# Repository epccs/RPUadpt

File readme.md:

# RPUadpt (/w 328pb)

From <https://github.com/epccs/RPUadpt/>

## Overview

Shield used to connect a controller board to a multi-drop serial bus (e.g. [RPUbus]). Modular 8P8C connectors allow RJ-45 connectors and CAT5 to run the differential pairs between locations. The robust noise immunity of the differential pairs allows a host computer (e.g. Pi Zero with [RPUpi], or desktop with [USBuart]) to interface with and bootload the controller board(s) in noisy environments over serial hardware that can be physically secured.

[RPUbus]: https://rpubus.org/
[USBuart]: https://github.com/epccs/Driver/tree/master/USBuart
[RPUpi]: https://github.com/epccs/RPUpi

An SPI interface with a level shifting buffer is available between the controller and computer. SPI is also wired to an optional header for a slave device (e.g. an [SD card]) that the controller can access. 

[SD card]: https://www.adafruit.com/product/254

I2C between the manager and the controller allows its program to read an address and make the serial connection active. I2C between manager and host allows the host computer to set a bootload address even when its local controller lacks I2C interfacing software. 

[RPUno]: https://github.com/epccs/RPUno
[Irrigate7]: https://github.com/epccs/Irrigate7
[Punica]: https://github.com/epccs/Punica

[Forum](https://rpubus.org/bb/viewforum.php?f=7)

[HackADay](https://hackaday.io/project/17719-rpuadpt)

## Status

[Available](https://rpubus.org/Order_Form.html)

This shield is programmed with an in-circuit serial programming tool that is able to handle the 3.3V ATmega328p target. I use an Arduino Uno with the [ArduinoISP] sketch and an SPI level shifter (e.g. [ICSP]). A Raspberry Pi should also work with the avrdude bit-bang (-c linuxgpio) or SPI (-c linuxspi) modes.

[ICSP]: https://github.com/epccs/Driver/tree/master/ICSP

[ArduinoISP]: https://github.com/arduino/Arduino/blob/master/build/shared/examples/11.ArduinoISP/ArduinoISP/ArduinoISP.ino

## [Hardware](./Hardware)

Hardware files and notes for referance.

## Example

This multi-drop serial bus allows multiple controller boards to be connected to a host serial port (UART). Crossover of the serial from the host computer occurs as it enters the transceivers on the shield. The differential pair from the transceives is run through patch cables (CAT5) between the controllers, so all the controllers see the same interface. 

The transceivers differential driver is enabled when a UART pulls its TX output low, which means no software [magic] is needed to operate the push to talk of the transceivers, though it is up to the user software to ensure the controllers talk in a reasonable way (e.g. without collision). Since the drivers in the transceivers only output an inverted level they can't cross conduct thus collisions don't damage the hardware. I see collisions when accidentally connecting two shields with the same address and both try to answer.

[magic]: https://github.com/pyserial/pyserial/blob/master/serial/rs485.py

In the above drawing, the computer can communicate with the three controller boards (an [RPUno], an [Irrigate7], and a [Punica]). The computer connected with USB to the RPUftdi shield can access the controller boards when the manager allows. The Raspberry Pi can also access the controller boards when the manager allows. Only one host computer should access the serial bus at a time. The RS-422 can be run a significate distance (perhaps over 1000 meters). 

In my firmware examples (e.g. see [RPUno]) a command processor is used to accept textual commands over the wired interface. The examples have a simple makefile that compiles the microcontroller firmware from the source. The host computers I use have the AVR toolchain from Debian installed and can compile and upload that firmware over the serial interface with the uploader tool (avrdude). 

The firmware examples use a makefile with a bootload rule (e.g. "make bootload") that uploads to the targets bootloader. Building without a rule (e.g. "make") compiles the firmware into a relocatable elf as expected but turns that into an Intel formate hex file, the bootload rule just sends that to the uploader tool. 

When the serial port on the host opens (e.g. PySerial, picocom, or the toolchain uploader tool) it pulls the nDTR and nRTS line low (they are active low) and that tells the manager firmware ([Remote] on RPUadpt and [Host2Remote] on [RPUftdi]) to send the bootload address on the DTR pair (i.e. start its bootloader with a reset), and lockout other host. PySerial needs to wait for a few seconds while the bootloader timeout finishes (an Arduino Uno also needs to wait for this timeout).

[Remote]: https://github.com/epccs/RPUadpt/tree/master/Remote
[Host2Remote]: https://github.com/epccs/RPUftdi/tree/master/Host2Remote

The manager can see (nDTR and nRTS) the host try to connect and if it is not blocked by another host will broadcast a bootload address. When the managers see the address on the DTR pair (note the local manager will also see it) then everything sets lockout_active except if the localhost_active is set then the host remains connected and also the addressed manager remains connected and sets bootloader_started. Again the address is in the manager on the shield, so the address follows the shield. Replacing the controller (e.g. swapping an [RPUno] with an [Irrigate7]) does not change the address, but replacing the shield does (the address on the shield may be programmed).

^6 has an ATmega328pb with a second I2C port, one for the control board and the other for the host. The details of how the host will use it are not yet known. Only the single board computers with Linux (e.g. Raspberry Pi) can do things with I2C at a reasonable price. For the host, I will probably expose the commands to read the local address and set the bootload address. If the host reads the local address then sneaky mode should probably end with a normal mode broadcast on the DTR pair (but that is TBD). 

^6 also has some SPI options that need to be tested, but until an evaluation is done using it is at your own risk.

## AVR toolchain

The core files for this board are in the /lib folder. Each example has its files and a Makefile in its own folder. The toolchain packages that I use are available on Debain, Ubuntu and Raspbian. 

```
sudo apt-get install git gcc-avr binutils-avr gdb-avr avr-libc avrdude
git clone https://github.com/epccs/RPUadpt
```

* [gcc-avr](https://packages.ubuntu.com/search?keywords=gcc-avr)
* [binutils-avr](https://packages.ubuntu.com/search?keywords=binutils-avr)
* [gdb-avr](https://packages.ubuntu.com/search?keywords=gdb-avr)
* [avr-libc](https://packages.ubuntu.com/search?keywords=avr-libc)
* [avrdude](https://packages.ubuntu.com/search?keywords=avrdude)

The ATmega328pb is not in mainline, so the files from Atmel [atpack] (DFP.1.2.209.atpack) are included in this repo for use with avr-gcc (GCC) 5.4.0. At the time of this writing Raspbian has avr-gcc (GCC) 4.9.2 which does not support atpack files.

[atpack]: http://packs.download.atmel.com/

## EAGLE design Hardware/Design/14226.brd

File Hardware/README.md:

# Hardware

## Overview

This shield board plugs into a control board (e.g. [RPUno], [Irrigate7], or [Punica]) to interface it with a multi-drop serial bus. 

[RPUno]: https://github.com/epccs/RPUno
[Irrigate7]: https://github.com/epccs/Irrigate7
[Punica]: https://github.com/epccs/Punica

## Inputs/Outputs/Functions

```
        Full Duplex serial RX and TX lines
        Half Duplex management line DTR
        RX, TX, and management lines connect to RS-485 tranceivers
        Differential pairs from transceivers allow multi-drop of the serial connections
        The transceivers receiver has Fail Safe so all see 0V as a HIGH.
        Power is taken from +5V of the control board.
        TWI0 (I2C) interface between local programable unit and manager.
        TWI1 (I2C) interface between local host and manager.
        IOFF buffers are used for UART and SPI host interface.
        IOFF allows the serial and control to remain functional when the host is powered down.
        UART and SPI interface buffers work with host voltage 5V to 1.8V.
```

## Uses

```
        Daisy chain serial from multiple control boards to a host.
        Use a point to point mode to bootload firmware to an addressed target.
        Use SPI to transfer data from a local host master to local programable unit slave.
        Or use the SPI local programable unit as master to operate a MicroSD card as slave.
```

## Notice

The serial port is a wired connection. The hardware is raw and lacks training wheels (i.e. it is not a polished product). The ATmega328pb toolchain is not widely available (e.g. {Debain: {stretch:no, buster:yes, sid:yes}} )

# Table Of Contents

1. [Status](#status)
2. [Design](#design)
3. [Bill of Materials](#bill-of-materials)
4. [How To Use](#how-to-use) 

# Status

```
        ^6  Done: Design, Layout, BOM, Review*, Order Boards, Assembly, Testing, Evaluation.
            WIP: 
            Todo:  
            *during review the Design may change without changing the revision.
            add IOFF buffer between host (e.g. offboard FTDI Friend) and tranceiver like RPUpi has
            add IOFF buffer between optional host SPI and controler like RPUpi
            add chip sellect from the host to IO10 (which has nSS, it is missing on RPUpi)
            SPI pinout can match MicroSD card breakout (https://www.adafruit.com/product/254)
            add a jumper to power the SPI from the controller (e.g. RPUno +5V)
            remove ADC6 connction to voltage divider of +5V pin.

        ^5 Done: Design, Layout, BOM, Review*, Order Boards, Assembly, Testing, Evaluation.
           removed from tindie is used in some locations.
```

Debugging and fixing problems i.e. [Schooling](./Schooling/)

Setup and methods used for [Evaluation](./Evaluation/)

# Design

The board is 0.063 thick, FR4, two layer, 1 oz copper with ENIG (gold) finish.

## Electrical Parameters (Typical)

```
        5V pin needs 150mA (RPUno has over 1A) to power RPU_BUS
        This is OSH so refer to the parts used for storage and operation limits.
```

## Electrical Schematic

## Testing

Check correct assembly and function with [Testing](./Testing/)

# Bill of Materials

The BOM is a CVS file, import it into a spreadsheet program like LibreOffice Calc (or Excel), or use a text editor.

Option | BOM's included
----- | ----- 
A. | [BRD] 
M. | [BRD] [SMD] [HDR] 
Y. | [BRD] [SMD] [HDR] [CAT5]

[BRD]: ./Design/14226BRD,BOM.csv
[SMD]: ./Design/14226SMD,BOM.csv
[HDR]: ./Design/14226HDR,BOM.csv
[CAT5]: ./Design/14226CAT,BOM.csv

# How To Use

## ICSP

[ArduinoISP] sketch is on an [Uno] and a level converter (e.g. [ICSP]) is between the boards. I then run the build rule (e.g. "make isp") to program the bus manager with the [Remote] firmware. With that, I can plug the RPUadpt into an RPUno and serial bootload the controller firmware (e.g. [Solenoid] with [K3]). An RPUftdi and Uno clone can be used with a host to communicate with the RPUadpt and its controller board. Additional boards will need the [Remote] firmware to have the bus address set in EEPROM.

[ArduinoISP]: https://github.com/arduino/Arduino/blob/master/build/shared/examples/11.ArduinoISP/ArduinoISP/ArduinoISP.ino
[Uno]: https://www.adafruit.com/product/50
[ICSP]: https://github.com/epccs/Driver/tree/master/ICSP
[Remote]: ../Remote
[Solenoid]: https://github.com/epccs/RPUno/tree/master/Solenoid
[K3]: https://github.com/epccs/Driver/tree/master/K3

__WARNING: The shield will be damaged if removed from a powered MCU board. Before separating the shield from the MCU board it is very important to check that all power sources are disconnected.__

The CAT5 needs wired just like an Ethernet cable following [T568A] (or T568B) method. 

[T568A]: https://en.wikipedia.org/wiki/Category_5_cable

Grounding should occur at one location only. If a RPUftdi is used then the host frame will be connected to the local earth grounding system through USB. Unfortunately, the ground wires within CAT5 will not survive a lightning strike and will bring it to the host. To reduce the risk run a #14 AWG ground wire between the remote device and the ground system connected to the host chassis. Also, the host chassis needs a good (#14 AWG or larger) wire to the same ground system (see NEC sec 250). 

The RX, TX, and DTR pair need a 100 Ohm termination on each end of the CAT5 daisy chain. I'm going to supply a RJ45 plug with terminations for now.

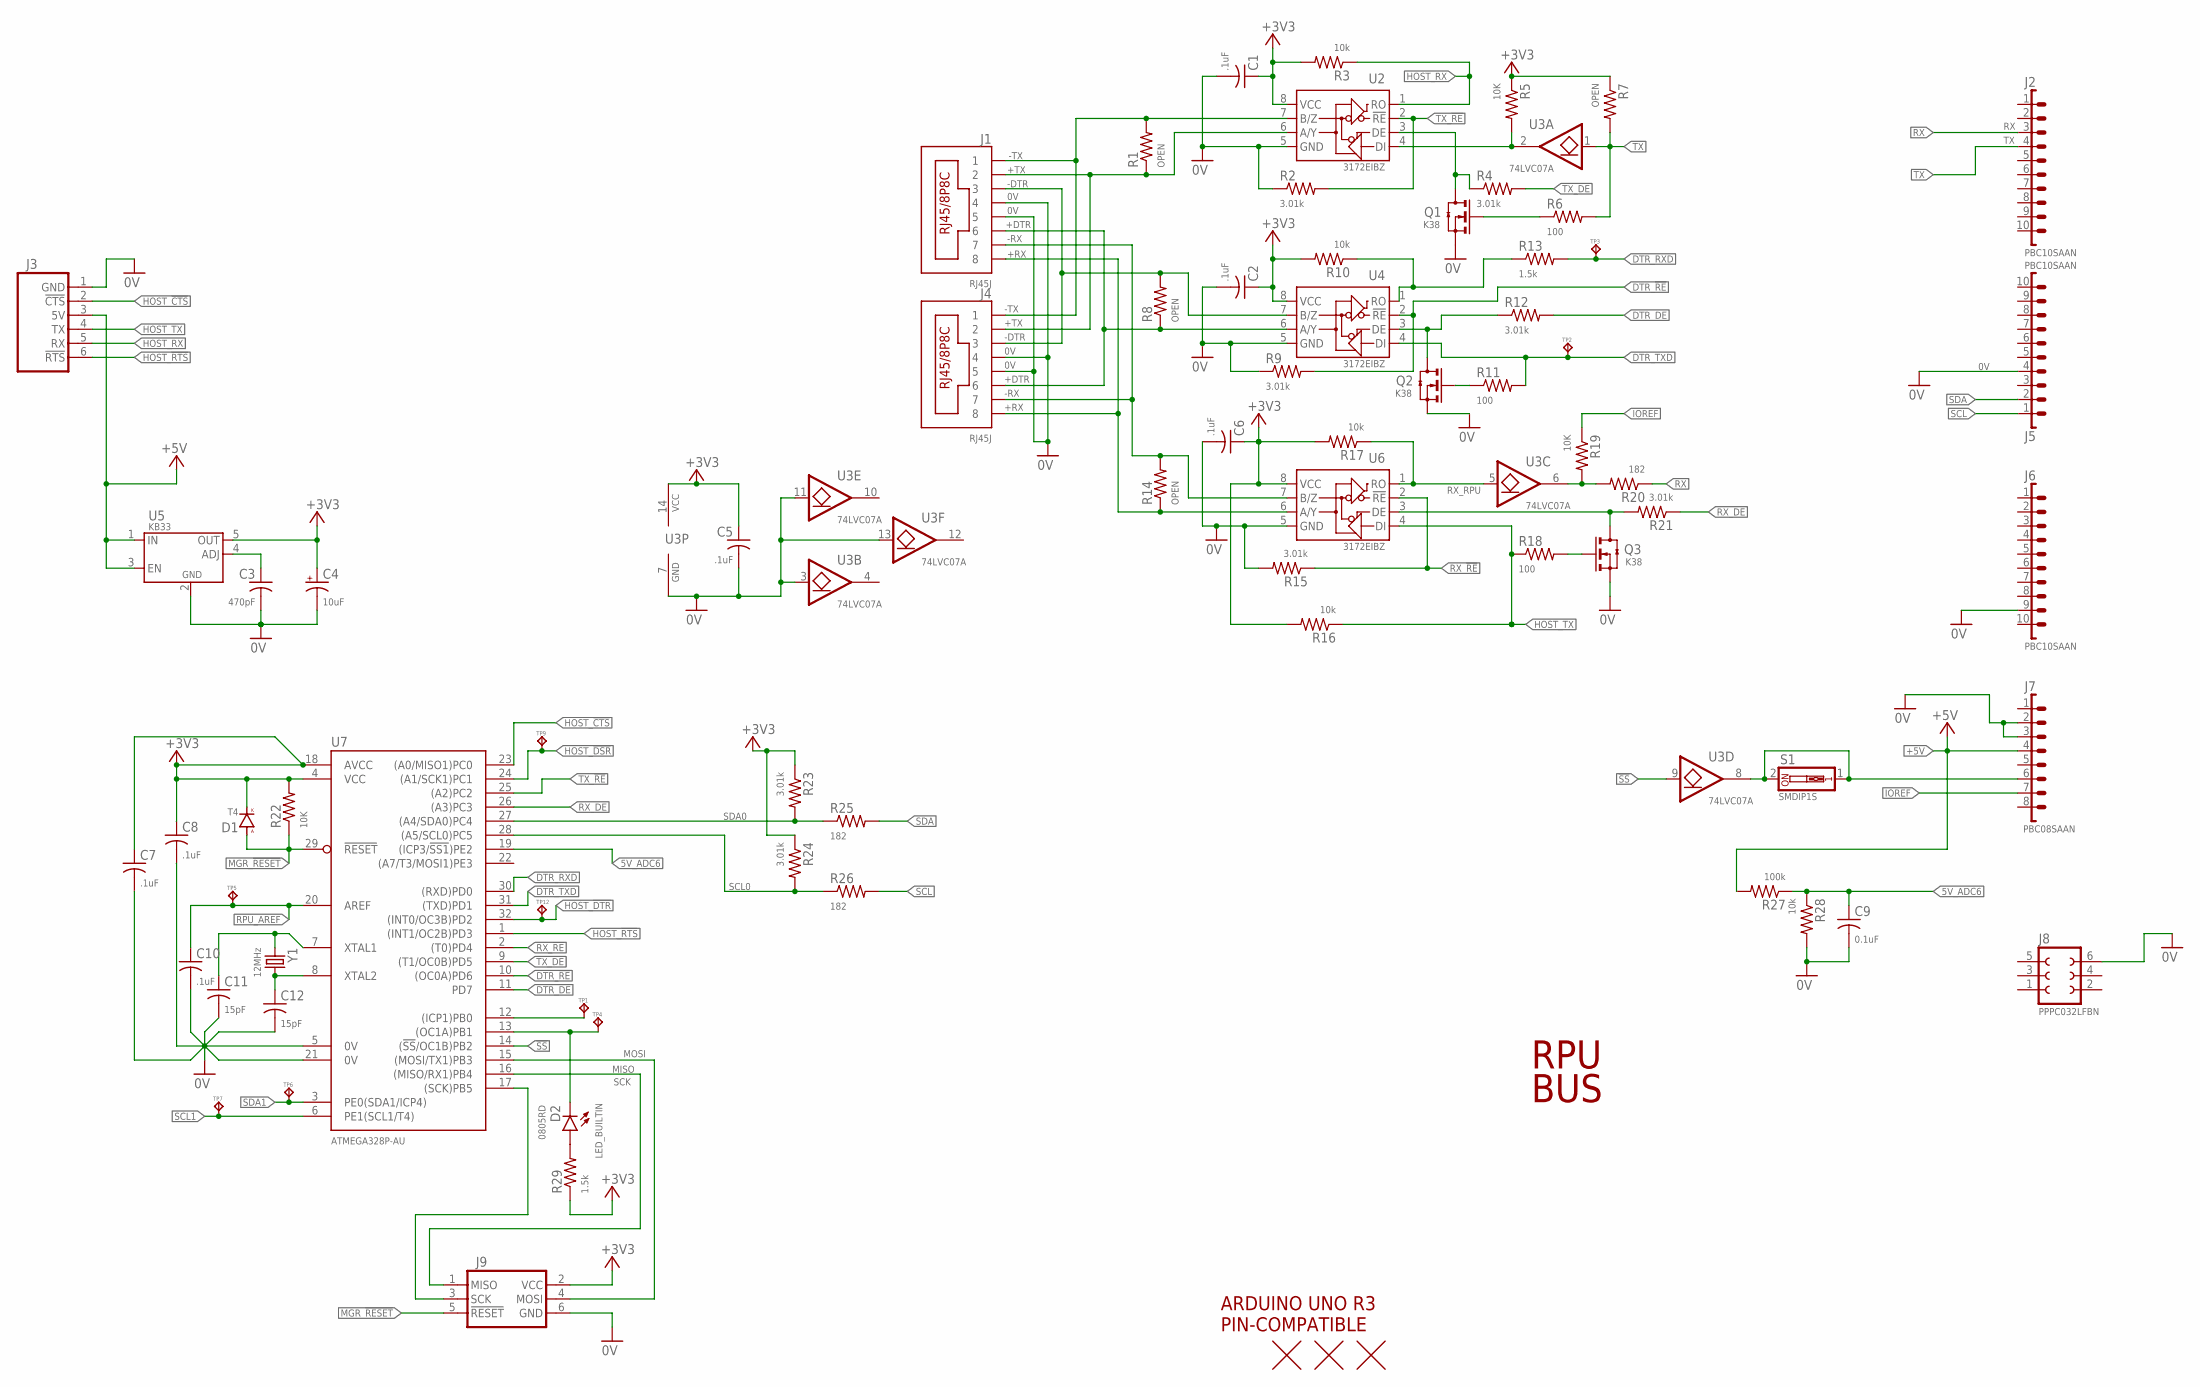
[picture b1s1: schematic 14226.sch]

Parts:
C1, C2, C5, C6, C7, C8, C10: .1uF; C0603(1608)
C3: 470pF; C0603(1608)
C4: 10uF; 3216
C9: 0.1uF; C0603(1608)
C11, C12: 15pF; C0603(1608)
D1: T4; SOD123
D2: 0805RD; C0805(2012)
J1, J4: RJ45J; RJ45-8HZT
J2, J5, J6: PBC10SAAN; 1X10
J3: FTDI-FRIEND
J7: PBC08SAAN; 1X8
J8: PPPC032LFBN; F2X3
J9: ISP-SPIPTH; ISP
Q1, Q2, Q3: K38; SOT23
R1, R7, R8, R14: OPEN; C0805(2012)
R2, R4, R9, R12, R15, R21, R23, R24: 3.01k; C0805(2012)
R3, R10, R16, R17, R28: 10k; C0805(2012)
R5, R19, R22: 10K; C0805(2012)
R6, R11, R18: 100; C0805(2012)
R13, R29: 1.5k; C0805(2012)
R20, R25, R26: 182; C0805(2012)
R27: 100k; C0805(2012)
S1: SMDIP1S; SMD-DIPSWITCH-1
TP1, TP2, TP3, TP4, TP5, TP6, TP7, TP9, TP12: TPPAD1-08; P1-08
U2, U4, U6: 3172EIBZ; SOIC8
U3: 74LVC07A; 14SOIC
U5: KB33; SOT23-5,SOT25
U7: ATMEGA328P-AU; TQFP32-08
U$1: ARDUINO-UNO; ARDUINO_UNO
U$2, U$3, U$4: FIDUCIAL1.27; FIDUCIAL-1.27
Y1: 12MHz; CSM-3X

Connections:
0V: C1.2, C2.2, C3.2, C4.-, C5.2, C6.2, C7.2, C8.2, C9.2, C10.2, C11.2, C12.2, J1.4, J1.5, J3.1 (GND), J4.4, J4.5, J5.4, J6.9, J7.2, J7.3, J8.6, J9.6 (GND), Q1.2(S) (S), Q2.2(S) (S), Q3.2(S) (S), R2.1, R9.1, R15.2, R28.2, U2.5 (GND), U3.3 (I), U3.7 (GND), U3.11 (I), U3.13 (I), U4.5 (GND), U5.2 (GND), U6.5 (GND), U7.5 (0V), U7.21 (0V)
5V_ADC6: C9.1, R27.1, R28.1, U7.19 ((ICP3/!SS1!)PE2)
!SS!: U3.9 (I), U7.14 ((!SS!/OC1B)PB2)
+3V3: C1.1, C2.1, C4.+, C5.1, C6.1, C7.1, C8.1, D1.C (K), J9.2 (VCC), R3.2, R5.1, R7.1, R10.2, R16.2, R17.2, R22.2, R23.1, R24.1, R29.1, U2.8 (VCC), U3.14 (VCC), U4.8 (VCC), U5.5 (OUT), U6.8 (VCC), U7.4 (VCC), U7.18 (AVCC)
+5V: J3.3 (5V), J7.4, R27.2, U5.1 (IN), U5.3 (EN)
+DTR: J1.6, J4.6, R8.1, U4.6 (A/Y)
+RX: J1.8, J4.8, R14.1, U6.6 (A/Y)
+TX: J1.2, J4.2, R1.1, U2.6 (A/Y)
-DTR: J1.3, J4.3, R8.2, U4.7 (B/Z)
-RX: J1.7, J4.7, R14.2, U6.7 (B/Z)
-TX: J1.1, J4.1, R1.2, U2.7 (B/Z)
DTR_!RE: R9.2, U4.2 (!RE), U7.10 ((OC0A)PD6)
DTR_DE: R12.2, U7.11 (PD7)
DTR_RXD: R13.2, TP3.TP, U7.30 ((RXD)PD0)
DTR_TXD: R11.2, TP2.TP, U4.4 (DI), U7.31 ((TXD)PD1)
HOST_!CTS: J3.2 (!CTS), U7.23 ((A0/MISO1)PC0)
HOST_!DSR: TP9.TP, U7.24 ((A1/SCK1)PC1)
HOST_!DTR: TP12.TP, U7.32 ((INT0/OC3B)PD2)
HOST_!RTS: J3.6 (!RTS), U7.1 ((INT1/OC2B)PD3)
HOST_RX: J3.5 (RX), R3.1, U2.1 (RO)
HOST_TX: J3.4 (TX), R16.1, R18.1, U6.4 (DI)
IOREF: J7.7, R19.1
LED_BUILTIN: D2.K, TP4.TP, U7.13 ((OC1A)PB1)
MGR_!RESET: D1.A, J9.5 (!RESET), R22.1, U7.29 (!RESET)
MISO: J9.1 (MISO), U7.16 ((MISO/RX1)PB4)
MOSI: J9.4 (MOSI), U7.15 ((MOSI/TX1)PB3)
unnamed: J7.6, S1.1, S1.2, U3.8 (O)
unnamed: R19.2, R20.2, U3.6 (O)
unnamed: Q3.3(D) (D), R21.2, U6.3 (DE)
unnamed: Q1.1(G) (G), R6.1
unnamed: Q1.3(D) (D), R4.1, U2.3 (DE)
unnamed: R10.1, R13.1, U4.1 (RO)
unnamed: Q2.3(D) (D), R12.1, U4.3 (DE)
unnamed: Q2.1(G) (G), R11.1
unnamed: C3.1, U5.4 (ADJ)
unnamed: Q3.1(G) (G), R18.2
unnamed: D2.A, R29.2
RPU_AREF: C10.1, TP5.TP, U7.20 (AREF)
RX: J2.3, R20.1
RX_!RE: R15.1, U6.2 (!RE), U7.2 ((T0)PD4)
RX_DE: R21.1, U7.26 ((A3)PC3)
RX_RPU: R17.1, U3.5 (I), U6.1 (RO)
SCK: J9.3 (SCK), U7.17 ((SCK)PB5)
SCL: J5.1, R26.2
SCL0: R24.2, R26.1, U7.28 ((A5/SCL0)PC5)
SCL1: TP7.TP, U7.6 (PE1(SCL1/T4))
SDA: J5.2, R25.2
SDA0: R23.2, R25.1, U7.27 ((A4/SDA0)PC4)
SDA1: TP6.TP, U7.3 (PE0(SDA1/ICP4))
SHUTDWN: TP1.TP, U7.12 ((ICP1)PB0)
TX: J2.4, R6.2, R7.2, U3.1 (I)
TX_!RE: R2.2, U2.2 (!RE), U7.25 ((A2)PC2)
TX_DE: R4.2, U7.9 ((T1/OC0B)PD5)
TX_RPU: R5.2, U2.4 (DI), U3.2 (O)
XTAL1: C11.1, U7.7 (XTAL1), Y1.1
XTAL2: C12.1, U7.8 (XTAL2), Y1.2

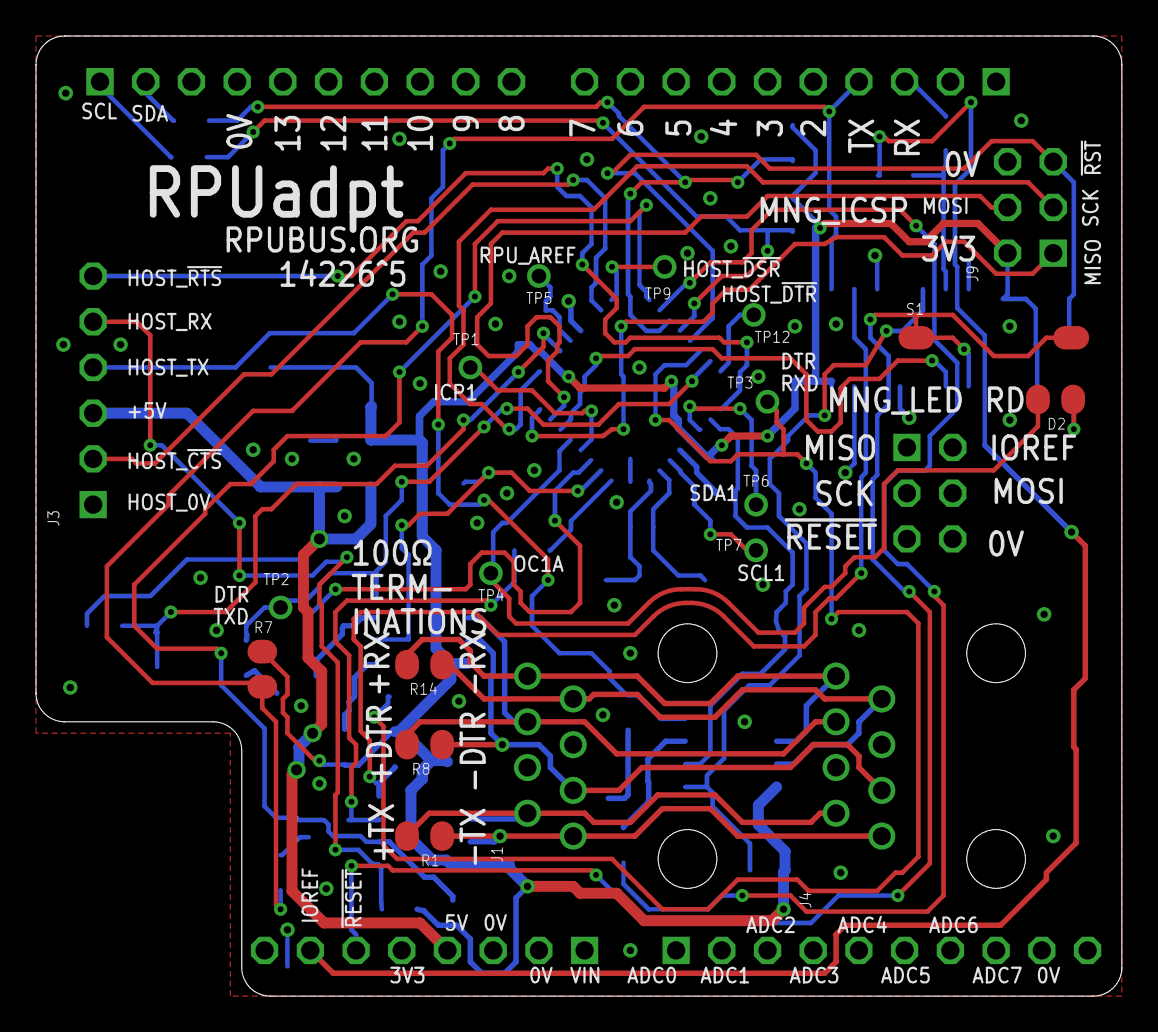
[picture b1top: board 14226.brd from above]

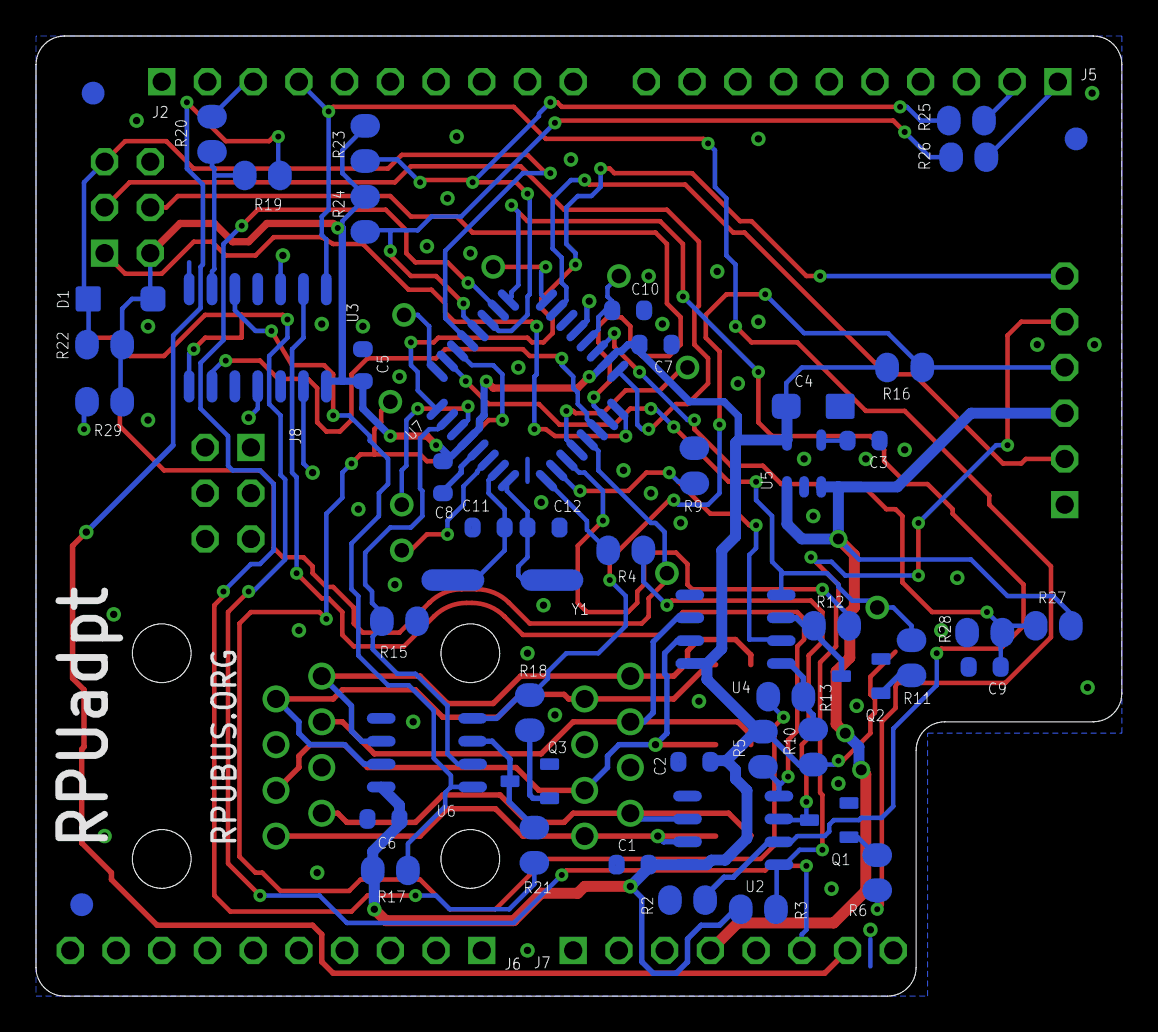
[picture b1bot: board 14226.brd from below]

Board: 2 copper layers, 60.3 x 53.3 mm, 76 parts (56 on the bottom side), 56 nets.

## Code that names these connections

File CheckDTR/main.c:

/* RPUadpt CheckDTR for hardware testing
 * Copyright (C) 2016 Ronald Sutherland
 *
 * This Library is free software: you can redistribute it and/or modify
 * it under the terms of the GNU General Public License as published by
 * the Free Software Foundation, either version 3 of the License, or
 * (at your option) any later version.
 *
 * This Library is distributed in the hope that it will be useful,
 * but WITHOUT ANY WARRANTY; without even the implied warranty of
 * MERCHANTABILITY or FITNESS FOR A PARTICULAR PURPOSE.  See the
 * GNU General Public License for more details.
 *
 * You should have received a copy of the GNU General Public License 
 * along with the Arduino DigitalIO Library.  If not, see
 * <http://www.gnu.org/licenses/>.
 *
 * story: first ^3 board had a little whisker of solder between DTR_RXD and DTR_TXD
 * three days was spent chasing the ghost.
 */ 

#include <util/delay.h>
#include <avr/io.h>
#include "../lib/timers.h"
#include "../lib/pin_num.h"
#include "../lib/pins_board.h"

static unsigned long blink_started_at;

void blink(uint8_t count)
{
    unsigned long kRuntime;
    
    for (uint8_t i=0 ;i<count; i++)
    {
        digitalToggle(LED_BUILTIN);
        kRuntime = 0;
        blink_started_at = millis();
        while (kRuntime <= 300) // wait for 1/10 second
        {
            kRuntime = millis() - blink_started_at;
        }
        digitalToggle(LED_BUILTIN);
        kRuntime = 0;
        blink_started_at = millis();
        while (kRuntime <= 300) // wait for 1/10 second
        {
            kRuntime = millis() - blink_started_at;
        }
    }
}

int main(void)
{
    pinMode(LED_BUILTIN,OUTPUT);
    digitalWrite(LED_BUILTIN,LOW);
    
    // set DTR transceiver
    pinMode(DTR_TXD,OUTPUT);
    digitalWrite(DTR_TXD,LOW);
    pinMode(DTR_DE,OUTPUT);
    digitalWrite(DTR_DE,HIGH);
    pinMode(DTR_nRE,OUTPUT);
    digitalWrite(DTR_nRE,LOW);

    // set TX and RX transceiver 
    pinMode(TX_DE,OUTPUT);
    digitalWrite(TX_DE,HIGH);
    pinMode(RX_DE,OUTPUT);
    digitalWrite(RX_DE,HIGH);
    // note TX_nRE and RX_nRE each have a pull down and thus do not need changed
    
    initTimers(); //Timer0 Fast PWM mode, Timer1 & Timer2 Phase Correct PWM mode.

    sei(); // Enable global interrupts to start TIMER0

    while (1) 
    {
        _delay_ms(4000);

        // set DTR transceiver DI input with 0V.
        digitalWrite(DTR_TXD,LOW);
        // set DTR transceiver DTR_DE HIGH to drive DTR pair, R12 has 3.3V.
        digitalWrite(DTR_DE,HIGH);
        // set DTR_nRE LOW cause transceiver to copy DTR pair to RO output
        digitalWrite(DTR_nRE,LOW);
        
        // DTR pair should be driven LOW by DI and copy its value to RO
        do
        {    
            blink(1);
            _delay_ms(1000);
        } while (digitalRead(DTR_RXD) != LOW);

        // set DTR transceiver DI input with 3.3V should cause an undriven pair
        digitalWrite(DTR_TXD,HIGH);

        // a High on DTR_TXD causes Q2 to pull down DTR_DE so the
        // DTR pair should be undriven which is seen at RO as a HIGH 
        do
        {    
            blink(2);
            _delay_ms(1000);
        } while(digitalRead(DTR_RXD) != HIGH);
 
        digitalWrite(DTR_DE,LOW);
        // set DTR_nRE HIGH to disconnect transceiver so R10 pulls up RO output
        digitalWrite(DTR_nRE,HIGH);
        digitalWrite(DTR_TXD,LOW);

        // DTR pair should be driven LOW but RO is disconnected and should pull-up to PASS
        do
        {    
            blink(3);
            _delay_ms(1000);
        } while (digitalRead(DTR_RXD) != HIGH);

        // set DTR_DE HIGH to copy DI onto DTR pair.
        digitalWrite(DTR_DE,HIGH);

        // DTR pair should not be driven and RO is disconnected and should pull-up to PASS
        do
        {    
            blink(4);
            _delay_ms(1000);
        } while (digitalRead(DTR_RXD) != HIGH);
    }    
}

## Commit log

2015-09-29 :octocat: Added .gitattributes
2015-09-29 fuse settings
2015-09-29 Blink
2015-09-29 LED not fully off due to 5V, fix by cycling between input and output
2015-09-29 readme wording
2015-09-30 more notes
2015-09-30 try to fix links
2015-11-16 project file
    I don't like the project file in the repo but ...
2015-11-16 Blink for arduino
2015-12-06 testing flow control lines
    ATtiny1634's PA3 has an issue as input
2015-12-06 fix readme markdown
2015-12-06 typo
2015-12-06 ArduinoISP sketch is from Arduino IDE 1.6.6
2015-12-06 poor wording
2016-08-21 BlinkLED: for ^3
    switching to Makefiles
2016-08-23 CheckDTR: chasing a ghost
2016-08-24 CheckDTR: set TX_DE and RX_DE also
2016-09-04 Remote: take byte on DTR pair
    and activate local MCU bootloader
2016-09-10 Remote: sorting out issues
    a lot like Remote2Host on RPUftdi
2016-09-11 Remote: updates from Mercurial repo
    lockout everything if host is foreign but only mcu if host is local
    disconnect when DTR pair has byte > 0x7F, start idea of a bus error
    char is like an int8_t on AVR but I thunked with uint8_t
    need improved host_is_foreign logic
2016-09-28 Remote: work on logic
2016-09-29 Remote: broadcast normal mode only if localhost_active
2016-11-05 CheckDTR: ^4 board tested
2016-11-16 Hardware: add schematic
2016-11-16 Hardware: add board
2016-11-18 Remote: don't connect mcu if not rpu aware
2017-01-02 Remote: broadcast after I2C read of rpu_addr /w bootloader_started
2017-01-02 Remote: save rpu_bus address to eeprom
2017-01-03 Hardware: reorg, add schooling
2017-01-05 Remote: add host shutdown on ICP1
2017-01-08 Remote: don't blink when told to halt
2017-01-14 Hardware: add evaluation and testing
2017-01-15 Hardware: ^5 review
2017-01-25 Hardware: ^5 more review
2017-01-26 Hardware: example
2017-03-11 Hardware: ^5 testing
2017-03-13 Hardware: ^5 more testing
2017-03-21 Hardware: ^5 evaluation south wall enclosure
2017-03-26 Hardware: use 12MHz crystal
2017-03-26 Hardware: add bus termination
2017-04-01 Hardware: through hole parts used for bus termination
2017-04-03 Hardware: add tindie link and remote reset evaluation
2017-04-19 Tindie, icsp tool links
2017-04-19 status icon
2017-04-19 markdown wrong way to do links
2017-05-22 Remote: sync with Host2Remote, use makefile to config
2017-05-22 RPUadpt: crystal capacitors, eagle is not for open hardware
2017-05-25 Remote: add lockout to status and rename rxBuffer as i2cBuffer
2017-05-25 Remote: RS-422 is using 38400 bit/s
2017-05-26 Hardware: match node names on schmatic with firmware
2017-05-26 Hardware: node names are used as macro names and must be C identifiers
2017-10-01 readme
2017-11-17 Hardware: ^6 changes lots, but the RS-422 as a remote should not have changed
2017-11-17 documentation
2017-11-17 antecedently is no accident
2018-05-01 BlinkLED: setup to work with 328pb
    prob should do this in a branch
2018-06-12 add atpack 209
2018-06-12 toolchain setup for 328pb
2018-06-16 notes for 328p branch
    keep a working branch for 328p
2018-06-16 master branch is for 328pb, 328p branch is for that mcu
2018-06-19 ^6 testing done, twi register names are not compatable so do twi0
2018-06-23 use objdump to list source code with disassembly
2018-06-25 BlinkLED: raspberry pi smbus toggles blink
2018-06-25 Hardware: eval i2c1 with i2c-debug
2018-06-26 Hardware: eval i2c1 with smbus from raspberry pi
2018-06-28 Remote: add twi1 /w commands 0, 2, 3, 6, 7 for host use
2018-07-01 Hardware: ^6 eval spi
2018-07-10 core: add missing wiring pin numbers
2018-07-13 https
2018-07-17 Hardware: some parts for tindie
2018-07-17 Hardware: note that ICSP needs to write efuse bit 3
2018-07-18 Hardware: bom, evaluation
2018-07-25 Hardware: ^6 evaluation with usb-uart
2018-08-10 Hardware: schematic notes
2019-01-27 rm tindie link
2019-02-28 Hardware: links to evaluation images, remove twi lib
2019-09-28 Hardware: schooling

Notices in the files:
parts and their libraries:
P-DCDC: Copyright (C) 2013 Ronald Steven Sutherland
under the terms of the GNU Free Documentation License, Version 1.2 or
any later version published by the Free Software Foundation; with no
C-C: Released under the Creative Commons
Attribution Share-Alike 3.0 License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
